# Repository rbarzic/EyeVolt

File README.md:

# Presentation

EyeVolt 2.0 is a **12-channel DC voltage monitor** **and** an **8-channel
programmable DC voltage generator**, both built around a single Raspberry Pi
Pico (the RP2040 `U9`).

On the **monitor** side the Pico continuously samples up to twelve external
voltages and streams the raw ADC readings out over USB-serial, exactly like
v1.1. On the **generation** side the Pico produces eight independent 0 - 3.3 V
outputs by low-pass-filtering eight PWM channels and buffering them; a feedback
multiplexer lets the Pico read its own generated outputs back.

A Python **Terminal User Interface (TUI)** on the PC displays the live
monitored values, progress bars and sparkline trends. The PC software can
optionally expose the readings through an **MCP (Model Context Protocol)
server** so that AI assistants / automation can query the voltages
programmatically.

> **Software status (2.0):** the firmware and PC software currently committed
> in this repository are the **v1.1 code** — they implement the original
> voltage-monitoring protocol only and do **not** yet match the 2.0 hardware.
> See the [Software status](#software-status-20) section below for what works
> today and what is still to be done.

The board has two monitoring domains (unchanged ranges from v1.1):

| Group | Channels | Full-scale | Conditioning | Routed to |
|-------|----------|-----------|--------------|-----------|
| Low-voltage  | 0 - 7  (8 ch) | 0 - 3.3 V | unity-gain buffer only               | MUX0 -> MUX1 (CH4) -> ADC0 (GP26) |
| High-voltage | 8 - 11 (4 ch) | 0 - 6.6 V | buffer + 2:1 resistive divider (÷2)  | MUX1 (CH0-CH3) -> ADC0 (GP26)      |

Because the RP2040 ADC only accepts 0 - 3.3 V, the high-voltage channels are
divided by two on the board (so 6.6 V at the input => 3.3 V at the ADC); the PC
software then multiplies back by two to display the true input voltage.

---

# Hardware

## What changed from v1.1

The 2.0 board keeps the exact same 12-channel voltage-monitoring function and
ranges as v1.1, but the analog multiplexing hardware was reworked, and a full
voltage-generation stage was added:

| Area | v1.1 | v2.0 |
|------|------|------|
| Monitor MUX topology | two independent 74HCT4051, each feeding its own ADC pin (MUX0->GP26, MUX1->GP27) | the two 74HCT4051 are **cascaded** and only **one** ADC pin is used for monitoring (MUX0 -> MUX1 CH4 -> GP26) |
| Monitor select lines | MUX0: S0/S1/S2 = GP10/11/12, MUX1: S0/S1/S2 = GP21/20/19 | MUX0: S0/S1/S2 = **GP12/11/10**, MUX1: S0/S1/S2 = **GP19/20/21** (S0 and S2 swapped on both muxes; `~E` and S1 unchanged) |
| High-voltage input nets | `V55IN0..3` | `V50IN0..3` (same ÷2 divider, same 0 - 6.6 V range — name only) |
| Voltage generation | none | **8 PWM outputs (GP2-GP9)** -> 2nd-order RC low-pass filter -> unity-gain buffer -> J2 output header |
| Output readback | none | a 3rd 74HCT4051 (U12) multiplexes the 8 generated outputs back to **GP27 (ADC1)** |
| Front-panel headers | J2/J3 = TFT/touchscreen (unused) | J2 = **DAC output IDC 2x20** (8 analog outputs + 8 raw PWM taps + power); TFT headers removed |

The input connector **J1** (2x10 box header) is pin-compatible with v1.1.

## Architecture (block-level)

```
                                       Voltage MONITORING                                  Voltage GENERATION
 +-----------+   +-----------------------+                                                    +--------------------+
 |           |V33>+-->|U3/U8 buffer x8 |---VBUFF0..7--> |     | (CH0..7)       PWM GP2..GP9 -->| R(10k)-C(1uF)-R-C  |--> OPA316 buffer x8
 |  J1 input |    |   (0-3.3V domain)  |                 |     |                              |   2nd-order LPF    |     (U4-7,U13-16)
 | connector |    +-----------------------+               |     |                              +--------------------+          |
 | 2x10 box  |            |                              | U11 | (MUX0)                                              0R  | OUT_LINK
 | header    |V50>--+-->|U1 buffer x4|--+  +---+         | 8:1 | ----------+                                           |
 |           |    |   |(high-V in)  |  +->|/2 |->|U2|--> |     |           |   +--------------------+                     |
 |           |    |   +-------------+--+  +---+  (x4)    +-----+           |   | U12 74HCT4051      |                     |
 |           |    |        100k/100k divider               |CH4|----------->| DAC feedback mux   |<--- DAC_OUT0..7 <----+
 |           |    |                                         |     |           | (U12)              |
 +-----------+    |    +-->|U2 buffer x4|---VBUFF8..11--> | U10 | (MUX1)   +--------------------+
                  |    |   |(after div) |                  | 8:1 |                       | common
                  |    |   +------------+                  |     | (CH0..3=HV, CH4=MUX0, | -> GP27 / ADC1 (readback)
                  |    +----------------------------------->|     |  CH5..7=spare)
                                                       +----+-----+
                                                       | common -> GP26 / ADC0 (monitor)
                                                       +----------+
                                                           Raspberry Pi Pico (U9)
        USB-CDC serial  (9600 8N1)  ----> PC running eyevolt_mcp.py
```

In words (monitoring path):

1. The voltages to be measured arrive on connector **J1** (a 2x10 box header).
2. Every input is **buffered** by a rail-to-rail CMOS op-amp configured as a
   unity-gain voltage follower, giving the circuit a very high input impedance
   so it does not perturb the device under test.
   * Low-voltage inputs `V33IN0..3` -> `U3` (MCP6L04 quad); `V33IN4..7` -> `U8`
     (MCP6L04 quad).
   * High-voltage inputs `V50IN0..3` -> `U1` (MCP6L04 quad), then a **100 k /
     100 k divider** (÷2), then buffered again by `U2` (MCP6L04 quad) so the
     divider node is not loaded.
3. The 8 low-voltage buffered signals (`VBUFF0..7`) feed **MUX0** (`U11`, a
   74HCT4051 8:1 analog multiplexer).
4. The 4 high-voltage buffered signals (`VBUFF8..11`) feed channels CH0-CH3 of
   **MUX1** (`U10`, also a 74HCT4051). **MUX0's common output is routed into
   MUX1's CH4 input**, so MUX1 selects between the 4 HV channels and the whole
   MUX0 bank. CH5-CH7 of MUX1 are spare (currently unused).
5. **MUX1's common output goes to ADC0 (GP26)** — this is the only ADC pin used
   for monitoring. The Pico enables MUX1, selects CH4 to reach the MUX0 bank,
   then cycles MUX0 through its 8 channels; for HV channels it selects CH0-CH3
   directly.

Generation path:

1. The Pico generates eight independent PWM signals on **GP2..GP9**
   (`DAC_PWM0..7`).
2. Each PWM signal passes through a **2nd-order passive RC low-pass filter**
   (10 kΩ + 1 µF, then 10 kΩ + 1 µF; per-stage cutoff ≈ 16 Hz) which converts
   the duty cycle into a DC level (0 - 3.3 V proportional to duty cycle).
3. Each filtered DC level is buffered by a unity-gain **OPA316** rail-to-rail
   op-amp (`U4,U5,U6,U7,U13,U14,U15,U16`).
4. A 0 Ω **OUT_LINK** jumper (`R25-R28`, `R45-R48`) ties each buffer output to
   its `DAC_OUTn` net on connector **J2** (the link can be removed to isolate
   or re-route a channel).
5. A third 74HCT4051 (**`U12`**, the *DAC feedback mux*) multiplexes the 8
   `DAC_OUT` signals onto **ADC1 (GP27)** so the firmware can read back every
   generated voltage and verify / trim it.

## Bill of materials (main components)

| Ref | Part | Function |
|-----|------|----------|
| U9 | Raspberry Pi Pico | MCU + dual ADC + USB-serial |
| U11 | 74HCT4051 | 8:1 analog multiplexer for the 3.3 V channels (**MUX0**) |
| U10 | 74HCT4051 | 8:1 analog multiplexer: HV channels CH0-3 + cascaded MUX0 on CH4 + spare CH5-7 (**MUX1**) |
| U12 | 74HCT4051 | 8:1 analog multiplexer for the 8 generated-output readback (**DAC feedback mux**) |
| U3, U8 | MCP6L04 (quad op-amp) | unity-gain buffers for the 8 low-voltage channels |
| U1 | MCP6L04 (quad op-amp) | input buffers for the 4 high-voltage channels |
| U2 | MCP6L04 (quad op-amp) | post-divider buffers for the 4 high-voltage channels |
| U4, U5, U6, U7, U13, U14, U15, U16 | OPA316 (single op-amp, SOT-23-5) | unity-gain buffers for the 8 generated outputs |
| R9-R12 | 100 kΩ | top leg of the 2:1 divider (one per HV channel) |
| R13-R16 | 100 kΩ | bottom leg of the divider to GND (one per HV channel) |
| R1-R8, R17-R24, R29-R44 | 10 kΩ | first and second series resistors of the 8 PWM low-pass filters |
| C3-C18, C27-C42 | 1 µF | filter capacitors of the 8 PWM low-pass filters (each with a DNP thru-hole alternate) |
| R25-R28, R45-R48 | 0 Ω (OUT_LINK) | jumpers linking each output buffer to its `DAC_OUT` net |
| C1-C2, C19-C26, C43-C47 | decoupling | local bypassing for the op-amps and the muxes |
| J1 | Conn_02x10 (2.54 mm box header) | voltage-monitor inputs + GND |
| J2 | IDC 2x20 (2.54 mm) | generation outputs: 8 analog `DAC_OUT`, 8 raw `DAC_PWM` taps, 5 V / 3.3 V / GND |
| H1-H4 | Mounting holes | mechanical |

The monitoring op-amps are Microchip **MCP6L04** (quad, 1 MHz, 85 µA,
rail-to-rail I/O) and the output buffers are TI **OPA316** (single, 2 MHz,
rail-to-rail I/O) — both low-cost, low-bias, supplied from the Pico's 3.3 V
rail. The pin-compatible MCP6024 and OPA4316 are kept as alternatives in
`doc/datasheets/opamp/`.

## Input connector J1 pinout (voltage monitor)

J1 is a 2x10 (2.54 mm) box header. The odd-numbered row carries the eight
low-voltage inputs (`V33IN0..7`); the even-numbered row carries the four
high-voltage inputs (`V50IN0..3`) plus ground. Pinout is compatible with v1.1.

> Pinout below is taken from the generated netlist (`hw/pcb/eyevolt.net`).
> Verify against the current schematic if in doubt.

| J1 pin | Signal   | Range      | EyeVolt channel |
|--------|----------|------------|-----------------|
| 1      | V33IN0   | 0 - 3.3 V  | ch 0  (MUX0 CH0) |
| 3      | V33IN1   | 0 - 3.3 V  | ch 1  (MUX0 CH1) |
| 5      | V33IN2   | 0 - 3.3 V  | ch 2  (MUX0 CH2) |
| 7      | V33IN3   | 0 - 3.3 V  | ch 3  (MUX0 CH3) |
| 9      | V33IN4   | 0 - 3.3 V  | ch 4  (MUX0 CH4) |
| 11     | V33IN5   | 0 - 3.3 V  | ch 5  (MUX0 CH5) |
| 13     | V33IN6   | 0 - 3.3 V  | ch 6  (MUX0 CH6) |
| 15     | V33IN7   | 0 - 3.3 V  | ch 7  (MUX0 CH7) |
| 2      | V50IN0   | 0 - 6.6 V  | ch 8  (MUX1 CH0) |
| 4      | V50IN1   | 0 - 6.6 V  | ch 9  (MUX1 CH1) |
| 6      | V50IN2   | 0 - 6.6 V  | ch 10 (MUX1 CH2) |
| 8      | V50IN3   | 0 - 6.6 V  | ch 11 (MUX1 CH3) |
| 10,12,14,16 | NC  | —          | not connected   |
| 17,18,19,20 | GND | —          | signal / return ground |

## Output connector J2 pinout (voltage generation)

J2 is a 2x20 (2.54 mm) IDC header. Each signal is bussed across a pair of pins
(standard IDC ribbon style). It exposes the 8 **buffered analog outputs**
(`DAC_OUT0..7`), the 8 **raw PWM taps** (`DAC_PWM0..7`, also driven by the
Pico), and the 5 V / 3.3 V / GND power rails.

| J2 pins      | Signal     | Direction | Notes |
|--------------|------------|-----------|-------|
| 1, 2, 3, 4   | GND        | —         | signal / return ground |
| 5, 6         | VDD50      | power out | 5 V (VBUS) rail |
| 7, 8         | VDD33      | power out | 3.3 V rail |
| 9, 10        | DAC_OUT7   | analog out| buffered generated output 7 |
| 11, 12       | DAC_OUT6   | analog out| buffered generated output 6 |
| 13, 14       | DAC_OUT5   | analog out| buffered generated output 5 |
| 15, 16       | DAC_OUT4   | analog out| buffered generated output 4 |
| 17, 18       | DAC_OUT3   | analog out| buffered generated output 3 |
| 19, 20       | DAC_OUT2   | analog out| buffered generated output 2 |
| 21, 22       | DAC_OUT1   | analog out| buffered generated output 1 |
| 23, 24       | DAC_OUT0   | analog out| buffered generated output 0 |
| 25, 26       | DAC_PWM7   | digital   | raw PWM tap 7 (driven by GP9) |
| 27, 28       | DAC_PWM6   | digital   | raw PWM tap 6 (driven by GP8) |
| 29, 30       | DAC_PWM5   | digital   | raw PWM tap 5 (driven by GP7) |
| 31, 32       | DAC_PWM4   | digital   | raw PWM tap 4 (driven by GP6) |
| 33, 34       | DAC_PWM3   | digital   | raw PWM tap 3 (driven by GP5) |
| 35, 36       | DAC_PWM2   | digital   | raw PWM tap 2 (driven by GP4) |
| 37, 38       | DAC_PWM1   | digital   | raw PWM tap 1 (driven by GP3) |
| 39, 40       | DAC_PWM0   | digital   | raw PWM tap 0 (driven by GP2) |

## Analog conditioning detail

* **Low-voltage channels (0-7):** each input drives the `+` input of an op-amp
  voltage follower whose output is shorted to its `-` input. The output
  (`VBUFF0..7`) goes directly to one of MUX0's analog inputs. No scaling — the
  displayed voltage equals the measured voltage (up to the 3.3 V rail).

* **High-voltage channels (8-11):** each input is first buffered (U1, high
  impedance), then split by a 100 k / 100 k divider to GND, then buffered again
  (U2) before reaching MUX1. The two-stage buffering keeps the divider node
  high-impedance and accurate. The ADC therefore sees `Vin / 2`, and the PC
  software restores the real value by multiplying by 2 (`raw / 65536 * 6.6`).

## Multiplexing (74HCT4051)

Each 74HCT4051 selects one of 8 analog inputs onto a common pin `A` according to
the 3-bit address `S2 S1 S0`, while `~E` (active-low enable) gates the output.
When `~E = 1` the switch is high-impedance. The Pico drives these logic pins
directly. On the board, VEE is tied to GND (single-supply operation, 0 - VCC
analog range) and VCC is the 3.3 V rail.

**Monitor cascade:** in 2.0, MUX0's common is wired to **MUX1 channel 4**, so
the firmware must (a) enable MUX1 and address CH4 to "see through" to the
8 low-voltage channels, then (b) cycle MUX0; the high-voltage channels are read
by addressing MUX1 CH0-CH3 directly. All twelve channels exit on **GP26**.

**Feedback mux:** `U12` independently switches the 8 generated `DAC_OUT`
signals onto **GP27** so each output voltage can be measured back by the Pico.

## PWM generation chain

Each of the 8 output channels is identical:

```
GPn (PWM) -- R 10k -- (C 1uF to GND) -- R 10k -- (C 1uF to GND) -- OPA316 unity buffer -- 0R OUT_LINK -- DAC_OUTn -> J2
```

This is a 2nd-order passive RC low-pass filter (per-stage cutoff
`1/(2*pi*10k*1uF) ≈ 16 Hz`) followed by a rail-to-rail unity-gain buffer. The
steady-state output is `duty * 3.3 V` over the 0 - 3.3 V range. The filter
strongly attenuates the PWM carrier so the output is essentially DC; the buffer
provides a low-impedance output to the load via J2.

## Power

The board is powered by the Pico's USB connection. The 3.3 V rail (`VDD33`)
powers the op-amps and the multiplexers and serves as the ADC reference. A 5 V
rail (`VDD50` = VBUS) is also present and is exposed on the J2 output header.

---

# Firmware (Pico, MicroPython)

Location: `sw/pico/micropython/main.py`. It is plain MicroPython using the
`machine` module; `boot.py` is empty (USB-CDC is configured in the firmware
image, not at run time).

## Pico pin mapping (2.0 hardware)

| GPIO | Direction | Net (schematic) | Purpose |
|------|-----------|-----------------|---------|
| GP2  | out (PWM) | DAC_PWM0 | generation PWM, output 0 |
| GP3  | out (PWM) | DAC_PWM1 | generation PWM, output 1 |
| GP4  | out (PWM) | DAC_PWM2 | generation PWM, output 2 |
| GP5  | out (PWM) | DAC_PWM3 | generation PWM, output 3 |
| GP6  | out (PWM) | DAC_PWM4 | generation PWM, output 4 |
| GP7  | out (PWM) | DAC_PWM5 | generation PWM, output 5 |
| GP8  | out (PWM) | DAC_PWM6 | generation PWM, output 6 |
| GP9  | out (PWM) | DAC_PWM7 | generation PWM, output 7 |
| GP10 | out | MUX0_S2 | MUX0 address bit 2 |
| GP11 | out | MUX0_S1 | MUX0 address bit 1 |
| GP12 | out | MUX0_S0 | MUX0 address bit 0 |
| GP13 | out | MUX0_EB | MUX0 enable (`~E`, active low) |
| GP14 | out | DACMUX_S1 | DAC feedback mux address bit 1 |
| GP15 | out | DACMUX_S0 | DAC feedback mux address bit 0 |
| GP16 | out | DACMUX_S2 | DAC feedback mux address bit 2 |
| GP17 | out | DACMUX_EB | DAC feedback mux enable (`~E`, active low) |
| GP18 | out | MUX1_EB | MUX1 enable (`~E`, active low) |
| GP19 | out | MUX1_S0 | MUX1 address bit 0 |
| GP20 | out | MUX1_S1 | MUX1 address bit 1 |
| GP21 | out | MUX1_S2 | MUX1 address bit 2 |
| GP26 | in (ADC0) | MON_ADC_A | MUX1 common -> reads all 12 monitor channels (LV via cascade) |
| GP27 | in (ADC1) | DAC_FB_A | DAC feedback mux common -> reads back the 8 generated outputs |

## Principle of operation (v1.1-compatible monitoring)

> The firmware currently checked in (`main.py`) is the **v1.1** firmware: it
> drives MUX0 / MUX1 as two independent muxes and reads **two** ADC pins
> (GP26 + GP27). On the **2.0** hardware this is incorrect — MUX1's select
> lines are remapped and all 12 channels now arrive on **GP26 only** (GP27 is
> the DAC-feedback ADC). See [Software status](#software-status-20).

The intended v1.1-compatible scan (to be re-implemented for 2.0) repeatedly:

1. Selects **MUX1 CH4** (the cascade), then scans **MUX0** channels 0..7: for
   each channel it writes the 3-bit MUX0 address, asserts `~E`, waits for the
   switch and buffer to settle, then reads **ADC0 (GP26)**.
2. Scans **MUX1** channels 0..3 (the HV channels) directly, reading ADC0.
3. Prints two text lines (one per group) over USB-serial.

`read_u16()` returns a 16-bit value (0..65535) proportional to the voltage at
the ADC pin relative to the 3.3 V reference. The firmware sends the *raw* value
unchanged; all scaling is done on the PC side.

## Serial protocol

USB-CDC, **9600 baud, 8N1**, ASCII text. The Pico emits two lines per cycle:

```
1::VVVVV VVVVV VVVVV VVVVV VVVVV VVVVV VVVVV VVVVV
2::VVVVV VVVVV VVVVV VVVVV
```

* `1::` introduces the 8 low-voltage channels (0..7), space-separated,
  zero-padded to 5 digits.
* `2::` introduces the 4 high-voltage channels (8..11), space-separated.
* Values are raw 16-bit ADC codes (0..65535).

There is no request/response framing and no checksum: the device streams
continuously and the host synchronises on the `1::` / `2::` headers. The 2.0
firmware will keep this protocol so the PC software and the MCP tools remain
backward-compatible.

---

# PC software

The recommended version is `sw/pc/eyevolt_mcp.py` (a richer superset of the
older `sw/pc/eyevolt_pc.py`). It is a single-file Python application built with
**Textual** (TUI), **pyserial-asyncio** (serial), and an optional **MCP over
SSE** server (Starlette + Uvicorn).

## Serial acquisition & scaling

`SerialProtocol` buffers bytes until a newline, then `process_line()` decodes
each frame:

* `1::` frame -> 8 integers, converted with `raw / 65536 * 3.3`  (volts, 0-3.3 V)
* `2::` frame -> 4 integers, converted with `raw / 65536 * 6.6`  (volts, 0-6.6 V)

The resulting 12 float values are pushed into the 12 display widgets.

## Terminal User Interface (TUI)

`SerialTUI` lays out **12 `VoltageDisplay` widgets in a 3x4 grid**. Each widget
contains a label with the channel name and current value, a progress bar
showing the value as a percentage of the channel full-scale (3.3 V for
channels 0-7, 6.6 V for channels 8-11), and a sparkline of recent history
(rolling window, default 128 samples). A colour scheme highlights abnormal
rails:

| Voltage | Colour |
|---------|--------|
| < 0.5 V     | white  |
| 0.5 - 0.8 V | yellow |
| 0.8 - 1.2 V | green  |
| >= 1.2 V    | red    |

## MCP server

When started with `--mcp`, an `EyeVoltMCPServer` runs an MCP server over
Server-Sent Events (SSE) on `127.0.0.1:8088` by default, in a background
thread. It exposes the live readings as tools that an MCP-compatible client
(e.g. an AI coding assistant) can call:

| Tool | Description |
|------|-------------|
| `get_voltages`        | All enabled channels as `{name: voltage}` |
| `get_voltage`         | One channel by name |
| `get_voltage_idx`     | One channel by index (0-11) |
| `get_channel_info`    | Full per-channel info (name, enabled, voltage, max) |
| `get_channel_history` | Sparkline history (percentages 0-100) for a named channel |

## Command-line usage

```
eyevolt_mcp.py [-h] [--text VAL=NAME,...] [--channel VAL=on|off,...]
               [--history N] [--mcp] [--mcp-host H] [--mcp-port P] [-v]
               PORT
```

* `PORT` — serial device, e.g. `/dev/ttyACM0` (Linux/macOS) or `COM3` (Windows).
* `--text` — rename channels, zero-based, e.g. `val0=VCORE,val1=VIO`.
* `--channel` — enable/disable channels, e.g. `val8=off,val9=off`. Channels not
  listed default to **on**; disabled channels show `----`.
* `--history` — sparkline length (default 128).
* `--mcp` — start the MCP/SSE server.
* `--mcp-host` / `--mcp-port` — MCP bind address (default `127.0.0.1:8088`).
* `-v` / `-vv` — info / debug logging.

Examples (see `sw/pc/readme.txt`):

```
./eyevolt_mcp.py --text val0=VCORE,val1=VIO /dev/ttyACM0

./eyevolt_mcp.py \
    --text val0=VCORE,val1=VMAX,val2=VMAIN,val3=VULP,val4=VPERIPH,\
val5=VCOREDIG,val6=VCORERAD,val7=VIO \
    --channel val8=off,val9=off,val10=off,val11=off \
    /dev/ttyACM0

./eyevolt_mcp.py --mcp /dev/ttyACM0        # also expose readings to MCP clients
```

---

# Software status (2.0)

The hardware described above is the **2.0** design, but the software in this
repository is still the **v1.1** implementation. Concretely:

| Feature | Status |
|---------|--------|
| 12-channel voltage monitoring (serial protocol `1::`/`2::`) | **Planned.** The protocol and PC side stay the same; only the Pico scan routine changes for the 2.0 MUX cascade / remapped select lines. The intent is for the device to expose the **same** v1.1 monitoring protocol by default. |
| Current `main.py` on 2.0 hardware | **Does not work as-is.** It uses two ADC pins and the v1.1 select-line mapping; on 2.0 all 12 channels arrive on GP26 and GP27 is the DAC-feedback ADC. |
| 8-channel voltage generation (PWM + filter + buffer) | **Not implemented.** Requires new firmware (PWM setup on GP2-GP9, duty-cycle commands) and PC/MCP tooling to set voltages. |
| Output readback via U12 / GP27 | **Not implemented.** Needs firmware + PC support to read and report generated voltages. |
| PC TUI / MCP server | **Working**, unchanged from v1.1 (monitoring only). |

### What the 2.0 firmware update needs (monitoring)

* Drive MUX0 select lines on the **new** GPIOs (S0=GP12, S1=GP11, S2=GP10).
* Drive MUX1 select lines on the **new** GPIOs (S0=GP19, S1=GP20, S2=GP21).
* To read the 8 low-voltage channels: enable MUX1, select **CH4** (cascade),
  then cycle MUX0 0..7 and read **ADC0 (GP26)**.
* To read the 4 high-voltage channels: select MUX1 **CH0..CH3** and read ADC0.
* Keep emitting the `1::` (8 values) / `2::` (4 values) lines so the PC
  software and MCP tools are unchanged.

### What the 2.0 generation feature needs

* PWM setup on GP2-GP9 with a carrier frequency well above the 16 Hz filter
  cutoff.
* A serial command set to set per-channel duty cycle (target voltage).
* Readback of the 8 `DAC_OUT` signals through U12 on **GP27 (ADC1)**.
* PC / MCP tooling to set and monitor the 8 generated voltages.

---

# Running the system end-to-end

1. **Flash the Pico** with a MicroPython image (USB-CDC enabled), then copy
   `sw/pico/micropython/main.py` onto it (the `sw/pico/micropython/Makefile`
   provides `make copy` via `rshell` and `make run` via `mpremote`). On power-up
   the Pico starts streaming `1::`/`2::` lines at 9600 baud.
2. **Set up the PC environment** (`requirements.txt`):
   `pip install -r requirements.txt` (textual, pyserial-asyncio, mcp, starlette,
   uvicorn, rich, ...).
3. **Run the TUI**, pointing it at the Pico's serial port and labelling the
   channels to match your DUT (example above).
4. **(Optional)** add `--mcp` and connect an MCP client to `http://127.0.0.1:8088/sse`.

> Note: step 1 assumes the firmware already matches the 2.0 monitoring routing.
> Until that update is done, the device will not produce correct readings on
> 2.0 hardware (see [Software status](#software-status-20)).

---

# End-to-end data path (summary)

```
MONITORING:
DUT rail -- J1 -- op-amp buffer (+÷2 divider on HV channels)
        -- 74HCT4051 MUX0 -> MUX1 CH4 / MUX1 CH0..3 (U11 -> U10, selected by GP10..13, GP19..21, GP18)
        -- Pico ADC0 (GP26)
        -- MicroPython reads raw 16-bit codes, prints "1::.." / "2::.."
        -- USB-CDC @9600 baud
        -- eyevolt_mcp.py (async serial reader)
        -- Textual TUI (value + bar + sparkline) and/or MCP/SSE server

GENERATION (not yet implemented):
PC target voltage -> serial command -> Pico sets PWM duty on GP2..GP9
        -> 2nd-order RC LPF (10k/1uF, ~16 Hz) -> OPA316 unity buffer
        -> 0R OUT_LINK -> DAC_OUT0..7 -> J2
        -> (readback) U12 74HCT4051 feedback mux -> Pico ADC1 (GP27)
```

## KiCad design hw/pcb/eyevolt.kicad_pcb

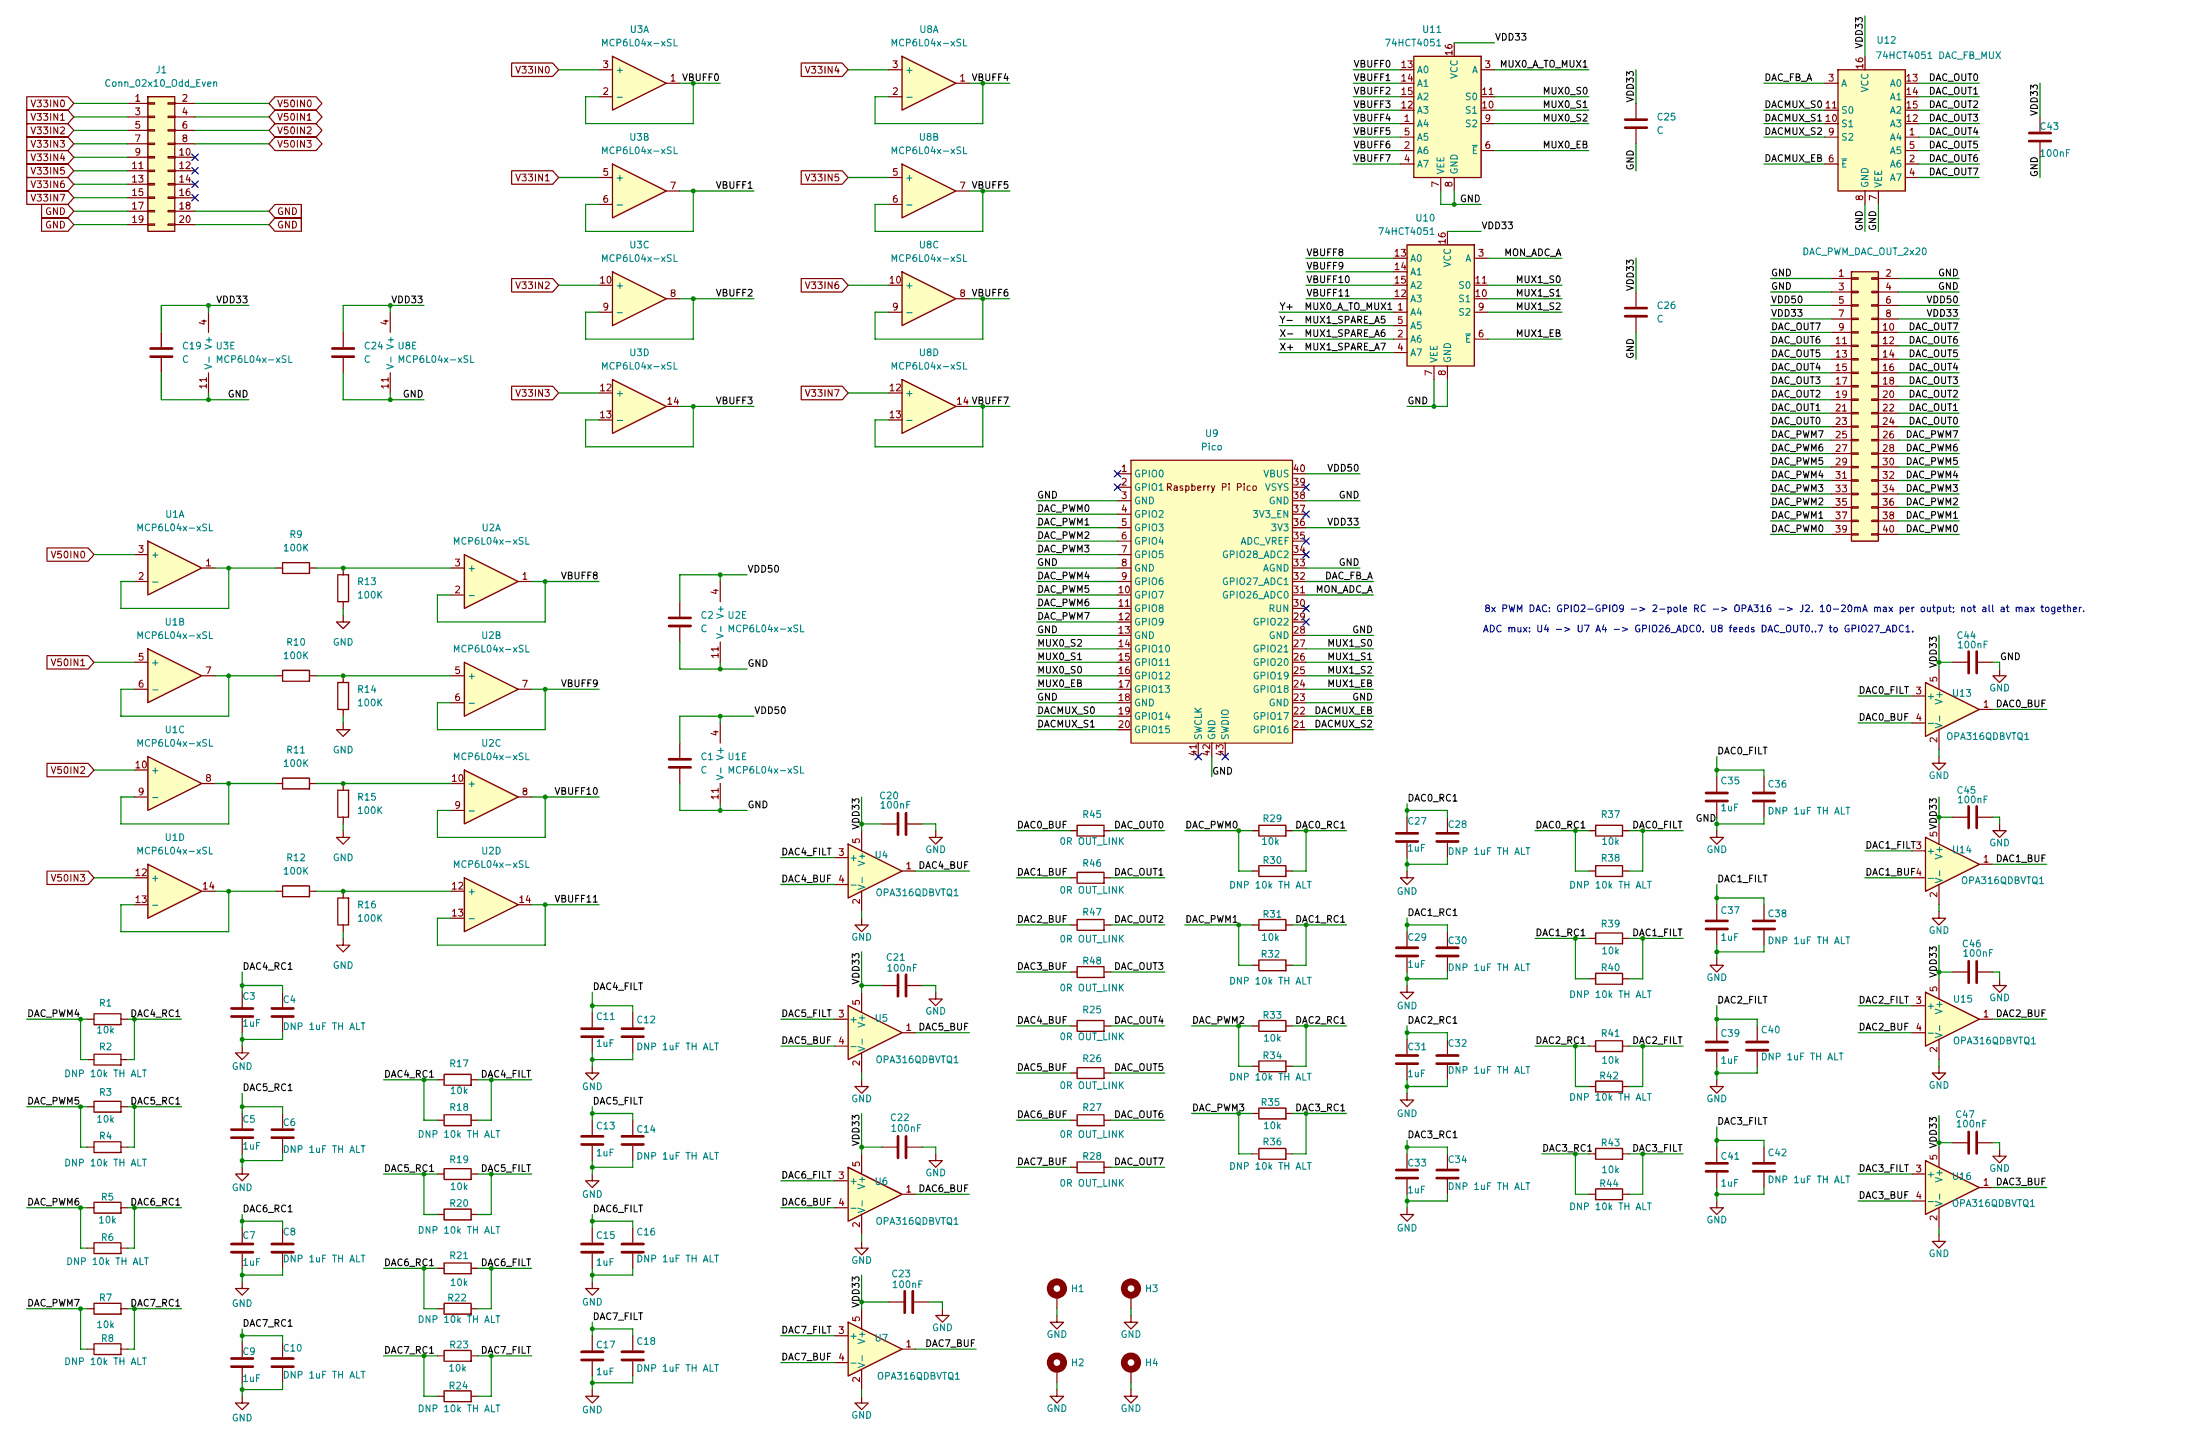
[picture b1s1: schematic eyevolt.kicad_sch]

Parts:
C1, C2, C19, C24, C25, C26: C; C_0805_2012Metric_Pad1.18x1.45mm_HandSolder
C3, C5, C7, C9, C11, C13, C15, C17, C27, C29, C31, C33, C35, C37, C39, C41: 1uF; C_0805_2012Metric_Pad1.18x1.45mm_HandSolder
C4, C6, C8, C10, C12, C14, C16, C18, C28, C30, C32, C34, C36, C38, C40, C42: DNP 1uF TH ALT; C_Disc_D5.0mm_W2.5mm_P5.00mm
C20, C21, C22, C23, C43, C44, C45, C46, C47: 100nF; C_0805_2012Metric
H1, H2, H3, H4: MountingHole_Pad; MountingHole_3.5mm_Pad_Via
J1: Conn_02x10_Odd_Even; PinHeader_2x10_P2.54mm_Horizontal
J2: DAC_PWM_DAC_OUT_2x20; IDC-Header_2x20_P2.54mm_Horizontal
R1, R3, R5, R7, R17, R19, R21, R23, R29, R31, R33, R35, R37, R39, R41, R43: 10k; R_0805_2012Metric_Pad1.20x1.40mm_HandSolder
R2, R4, R6, R8, R18, R20, R22, R24, R30, R32, R34, R36, R38, R40, R42, R44: DNP 10k TH ALT; R_Axial_DIN0207_L6.3mm_D2.5mm_P7.62mm_Horizontal
R9, R10, R11, R12, R13, R14, R15, R16: 100K; R_0805_2012Metric_Pad1.20x1.40mm_HandSolder
R25, R26, R27, R28, R45, R46, R47, R48: 0R OUT_LINK; R_0805_2012Metric_Pad1.20x1.40mm_HandSolder
U1, U2, U3, U8: MCP6L04x-xSL; SOIC-14_3.9x8.7mm_P1.27mm
U4, U5, U6, U7, U13, U14, U15, U16: OPA316QDBVTQ1; SOT-23-5
U9: Pico; RPi_Pico_SMD_TH
U10, U11: 74HCT4051; SOIC-16_3.9x9.9mm_P1.27mm
U12: 74HCT4051 DAC_FB_MUX; SOIC-16_3.9x9.9mm_P1.27mm

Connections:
/DAC0_BUF: R45.1, U13.1, U13.4 (-)
/DAC0_FILT: C35.1, C36.1, R37.2, R38.2, U13.3 (+)
/DAC0_RC1: C27.1, C28.1, R29.2, R30.2, R37.1, R38.1
/DAC1_BUF: R46.1, U14.1, U14.4 (-)
/DAC1_FILT: C37.1, C38.1, R39.2, R40.2, U14.3 (+)
/DAC1_RC1: C29.1, C30.1, R31.2, R32.2, R39.1, R40.1
/DAC2_BUF: R47.1, U15.1, U15.4 (-)
/DAC2_FILT: C39.1, C40.1, R41.2, R42.2, U15.3 (+)
/DAC2_RC1: C31.1, C32.1, R33.2, R34.2, R41.1, R42.1
/DAC3_BUF: R48.1, U16.1, U16.4 (-)
/DAC3_FILT: C41.1, C42.1, R43.2, R44.2, U16.3 (+)
/DAC3_RC1: C33.1, C34.1, R35.2, R36.2, R43.1, R44.1
/DAC4_BUF: R25.1, U4.1, U4.4 (-)
/DAC4_FILT: C11.1, C12.1, R17.2, R18.2, U4.3 (+)
/DAC4_RC1: C3.1, C4.1, R1.2, R2.2, R17.1, R18.1
/DAC5_BUF: R26.1, U5.1, U5.4 (-)
/DAC5_FILT: C13.1, C14.1, R19.2, R20.2, U5.3 (+)
/DAC5_RC1: C5.1, C6.1, R3.2, R4.2, R19.1, R20.1
/DAC6_BUF: R27.1, U6.1, U6.4 (-)
/DAC6_FILT: C15.1, C16.1, R21.2, R22.2, U6.3 (+)
/DAC6_RC1: C7.1, C8.1, R5.2, R6.2, R21.1, R22.1
/DAC7_BUF: R28.1, U7.1, U7.4 (-)
/DAC7_FILT: C17.1, C18.1, R23.2, R24.2, U7.3 (+)
/DAC7_RC1: C9.1, C10.1, R7.2, R8.2, R23.1, R24.1
/DACMUX_EB: U9.22 (GPIO17), U12.6 (~E)
/DACMUX_S2: U9.21 (GPIO16), U12.9 (S2)
/DAC_FB_A: U9.32 (GPIO27_ADC1), U12.3 (A)
/DAC_OUT0: J2.23, J2.24, R45.2, U12.13 (A0)
/DAC_OUT1: J2.21, J2.22, R46.2, U12.14 (A1)
/DAC_OUT2: J2.19, J2.20, R47.2, U12.15 (A2)
/DAC_OUT3: J2.17, J2.18, R48.2, U12.12 (A3)
/DAC_OUT4: J2.15, J2.16, R25.2, U12.1 (A4)
/DAC_OUT5: J2.13, J2.14, R26.2, U12.5 (A5)
/DAC_OUT6: J2.11, J2.12, R27.2, U12.2 (A6)
/DAC_OUT7: J2.9, J2.10, R28.2, U12.4 (A7)
/DAC_PWM0: J2.39, J2.40, R29.1, R30.1, U9.4 (GPIO2)
/DAC_PWM1: J2.37, J2.38, R31.1, R32.1, U9.5 (GPIO3)
/DAC_PWM2: J2.35, J2.36, R33.1, R34.1, U9.6 (GPIO4)
/DAC_PWM3: J2.33, J2.34, R35.1, R36.1, U9.7 (GPIO5)
/DAC_PWM4: J2.31, J2.32, R1.1, R2.1, U9.9 (GPIO6)
/DAC_PWM5: J2.29, J2.30, R3.1, R4.1, U9.10 (GPIO7)
/DAC_PWM6: J2.27, J2.28, R5.1, R6.1, U9.11 (GPIO8)
/DAC_PWM7: J2.25, J2.26, R7.1, R8.1, U9.12 (GPIO9)
/MON_ADC_A: U9.31 (GPIO26_ADC0), U10.3 (A)
/MUX0_A_TO_MUX1: U10.1 (A4), U11.3 (A)
/MUX0_EB: U9.17 (GPIO13), U11.6 (~E)
/MUX0_S0: U9.16 (GPIO12), U11.11 (S0)
/MUX0_S1: U9.15 (GPIO11), U11.10 (S1)
/MUX0_S2: U9.14 (GPIO10), U11.9 (S2)
/MUX1_EB: U9.24 (GPIO18), U10.6 (~E)
/MUX1_S1: U9.26 (GPIO20), U10.10 (S1)
/MUX1_SPARE_A5: U10.5 (A5)
/MUX1_SPARE_A6: U10.2 (A6)
/MUX1_SPARE_A7: U10.4 (A7)
/VBUFF0: U3.1, U3.2 (-), U11.13 (A0)
/VBUFF1: U3.6 (-), U3.7, U11.14 (A1)
/VBUFF2: U3.8, U3.9 (-), U11.15 (A2)
/VBUFF3: U3.13 (-), U3.14, U11.12 (A3)
/VBUFF4: U8.1, U8.2 (-), U11.1 (A4)
/VBUFF5: U8.6 (-), U8.7, U11.5 (A5)
/VBUFF6: U8.8, U8.9 (-), U11.2 (A6)
/VBUFF7: U8.13 (-), U8.14, U11.4 (A7)
/VBUFF8: U2.1, U2.2 (-), U10.13 (A0)
/VBUFF9: U2.6 (-), U2.7, U10.14 (A1)
/VBUFF10: U2.8, U2.9 (-), U10.15 (A2)
/VBUFF11: U2.13 (-), U2.14, U10.12 (A3)
/VDD33: C19.1, C20.1, C21.1, C22.1, C23.1, C24.1, C25.1, C26.1, C43.1, C44.1, C45.1, C46.1, C47.1, J2.7, J2.8, U3.4 (V+), U4.5 (V+), U5.5 (V+), U6.5 (V+), U7.5 (V+), U8.4 (V+), U9.36 (3V3), U10.16 (VCC), U11.16 (VCC), U12.16 (VCC), U13.5 (V+), U14.5 (V+), U15.5 (V+), U16.5 (V+)
/VDD50: C1.1, C2.1, J2.5, J2.6, U1.4 (V+), U2.4 (V+), U9.40 (VBUS)
GND: C1.2, C2.2, C3.2, C4.2, C5.2, C6.2, C7.2, C8.2, C9.2, C10.2, C11.2, C12.2, C13.2, C14.2, C15.2, C16.2, C17.2, C18.2, C19.2, C20.2, C21.2, C22.2, C23.2, C24.2, C25.2, C26.2, C27.2, C28.2, C29.2, C30.2, C31.2, C32.2, C33.2, C34.2, C35.2, C36.2, C37.2, C38.2, C39.2, C40.2, C41.2, C42.2, C43.2, C44.2, C45.2, C46.2, C47.2, H1.1 (1_1), H2.1 (1_1), H3.1 (1_1), H4.1 (1_1), J1.17, J1.18, J1.19, J1.20, J2.1, J2.2, J2.3, J2.4, R13.1, R14.1, R15.1, R16.1, U1.11 (V-), U2.11 (V-), U3.11 (V-), U4.2 (V-), U5.2 (V-), U6.2 (V-), U7.2 (V-), U8.11 (V-), U9.3 (GND), U9.8 (GND), U9.13 (GND), U9.18 (GND), U9.23 (GND), U9.28 (GND), U9.33 (AGND), U9.38 (GND), U9.42 (GND), U10.7 (VEE), U10.8 (GND), U11.7 (VEE), U11.8 (GND), U12.7 (VEE), U12.8 (GND), U13.2 (V-), U14.2 (V-), U15.2 (V-), U16.2 (V-)
unnamed: R9.1, U1.1, U1.2 (-)
unnamed: R10.1, U1.6 (-), U1.7
unnamed: R11.1, U1.8, U1.9 (-)
unnamed: R12.1, U1.13 (-), U1.14
unnamed: R9.2, R13.2, U2.3 (+)
unnamed: R10.2, R14.2, U2.5 (+)
unnamed: R11.2, R15.2, U2.10 (+)
unnamed: R12.2, R16.2, U2.12 (+)
V33IN0: J1.1, U3.3 (+)
V33IN1: J1.3, U3.5 (+)
V33IN2: J1.5, U3.10 (+)
V33IN3: J1.7, U3.12 (+)
V33IN4: J1.9, U8.3 (+)
V33IN5: J1.11, U8.5 (+)
V33IN6: J1.13, U8.10 (+)
V33IN7: J1.15, U8.12 (+)
V50IN0: J1.2, U1.3 (+)
V50IN1: J1.4, U1.5 (+)
V50IN2: J1.6, U1.10 (+)
V50IN3: J1.8, U1.12 (+)

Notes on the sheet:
8x PWM DAC: GPIO2-GPIO9 -> 2-pole RC -> OPA316 -> J2. 10-20mA max per output; not all at max together.
ADC mux: U4 -> U7 A4 -> GPIO26_ADC0. U8 feeds DAC_OUT0..7 to GPIO27_ADC1.

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
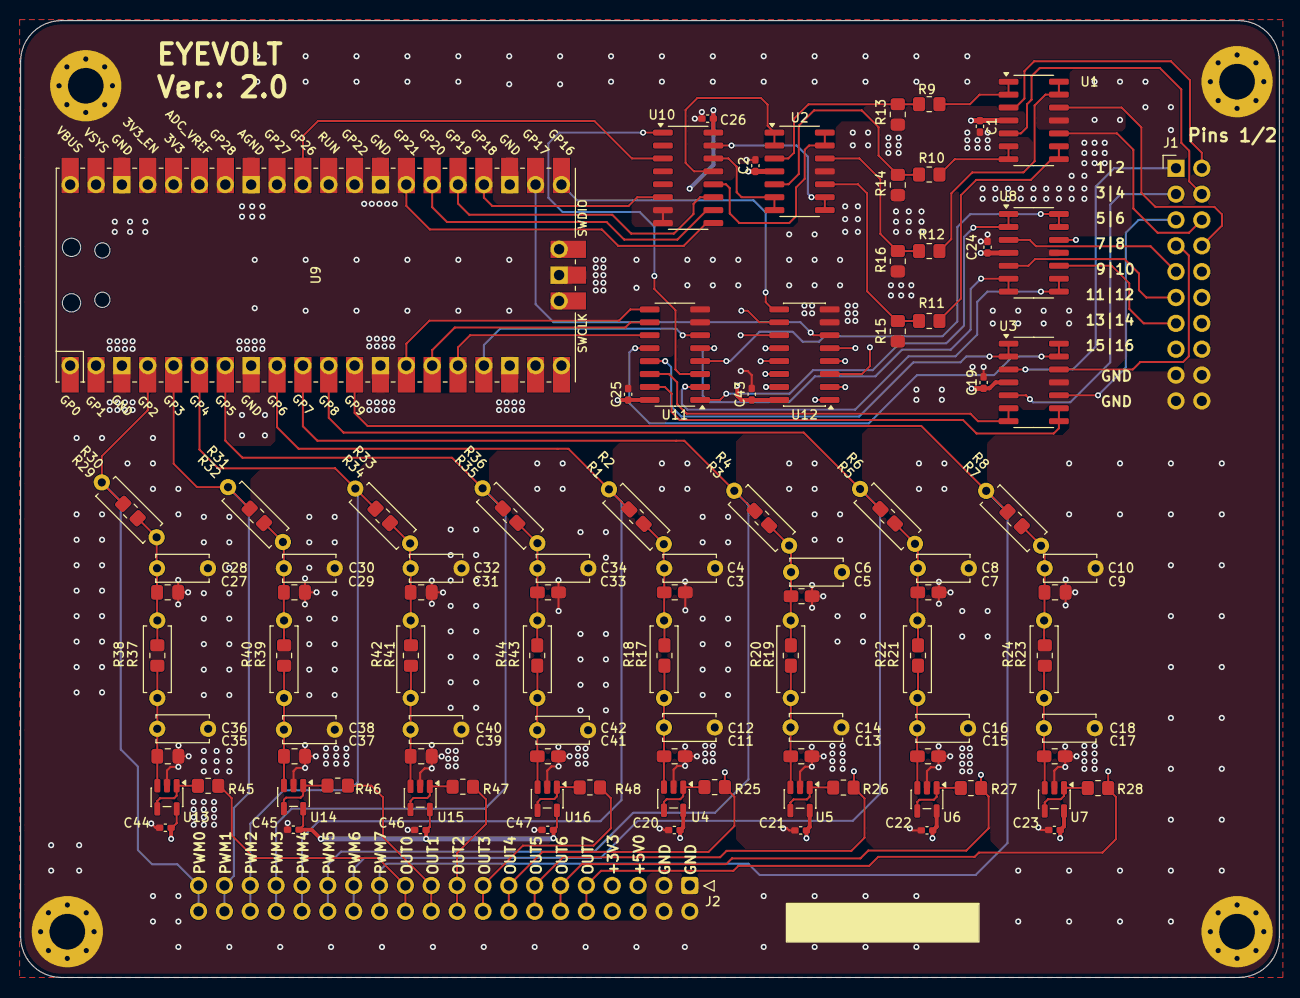
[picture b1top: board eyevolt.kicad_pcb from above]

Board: 4 copper layers, 123.7 x 94.0 mm, 117 parts (0 on the bottom side), 90 nets.

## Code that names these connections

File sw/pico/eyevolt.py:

from machine import Pin,ADC
from time import sleep

led = Pin('LED', Pin.OUT)
print('Blinking LED Example')

adc0 = ADC(26)
adc1 = ADC(27)

mux0_eb = Pin('GPIO13', Pin.OUT)
mux0_S0 = Pin('GPIO10', Pin.OUT)
mux0_S1 = Pin('GPIO11', Pin.OUT)
mux0_S2 = Pin('GPIO12', Pin.OUT)

mux1_eb = Pin('GPIO18', Pin.OUT)
mux1_S0 = Pin('GPIO21', Pin.OUT)
mux1_S1 = Pin('GPIO20', Pin.OUT)
mux1_S2 = Pin('GPIO19', Pin.OUT)


def mux0 (channel):
  b0 = channel & 1
  b1 = (channel & 2)>>1
  b2 = (channel & 4)>>2
  
  mux0_S0.value(b0) 
  mux0_S1.value(b1)
  mux0_S2.value(b2)
  mux0_eb.value(0)

def mux1 (channel):
  b0 = channel & 1
  b1 = (channel & 2)>>1
  b2 = (channel & 4)>>2
  
  mux1_S0.value(b0) 
  mux1_S1.value(b1)
  mux1_S2.value(b2)
  mux1_eb.value(0)

mux0(4)
mux1(0) 

while True:
  led.value(not led.value())
  adc_data0 = adc0.read_u16()
  adc_data1 = adc1.read_u16()
  print(f"ADC0 {(adc_data0 / 65535)*3.3}")
  print(f"ADC1 {(adc_data1 / 65535)*3.3*0.5}")
  
  sleep(0.5)

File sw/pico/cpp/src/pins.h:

#pragma once

//
// EyeVolt 2.0 — Pico (RP2040) hardware pin map.
//
// Source of truth for the v2.0 PCB. See the project README.md section
// "Pico pin mapping (2.0 hardware)". Key differences from v1.1:
//   * MUX0 and MUX1 are CASCADED; all 12 monitor channels exit on GP26 only.
//   * S0 and S2 are swapped on both monitor muxes vs v1.1.
//   * GP27 is now the DAC-feedback ADC (was MUX1 monitor ADC in v1.1).
//   * GP2-GP9 drive the 8 PWM generation outputs (new in v2.0).
//

namespace pins {

// ── Monitor mux MUX0 (U11): 8 low-voltage channels ──────────────────────────
// (S0/S2 swapped vs v1.1: v1.1 had S0=GP10, S2=GP12)
constexpr unsigned MUX0_S0 = 12;
constexpr unsigned MUX0_S1 = 11;
constexpr unsigned MUX0_S2 = 10;
constexpr unsigned MUX0_EN = 13;   // ~E, active low

// ── Monitor mux MUX1 (U10): HV channels CH0-3, cascade MUX0 on CH4 ───────────
// (S0/S2 swapped vs v1.1: v1.1 had S0=GP21, S2=GP19)
constexpr unsigned MUX1_S0 = 19;
constexpr unsigned MUX1_S1 = 20;
constexpr unsigned MUX1_S2 = 21;
constexpr unsigned MUX1_EN = 18;   // ~E, active low

// MUX1 channel that taps the cascaded MUX0 bank (low-voltage inputs).
constexpr unsigned MUX1_CASCADE_CHANNEL = 4;

// ── DAC feedback mux U12: reads back 8 generated outputs ─────────────────────
constexpr unsigned DACMUX_S0 = 15;
constexpr unsigned DACMUX_S1 = 14;
constexpr unsigned DACMUX_S2 = 16;
constexpr unsigned DACMUX_EN = 17;   // ~E, active low

// ── ADC inputs ───────────────────────────────────────────────────────────────
// RP2040 ADC input number (not the GPIO number): input 0 = GP26, input 1 = GP27.
constexpr unsigned ADC_MONITOR  = 0;   // GP26 — all 12 monitor channels (via MUX1)
constexpr unsigned ADC_READBACK = 1;   // GP27 — 8 generated-output readback (via U12)

constexpr unsigned ADC_MONITOR_PIN  = 26;
constexpr unsigned ADC_READBACK_PIN = 27;

// ── PWM generation outputs (GP2-GP9 → DAC_PWM0..7) ───────────────────────────
constexpr unsigned DAC_PWM_FIRST = 2;    // DAC_PWM0 = GP2
constexpr unsigned NUM_DAC_CHANNELS = 8;

// ── Channel counts ───────────────────────────────────────────────────────────
constexpr unsigned NUM_LV_CHANNELS      = 8;   // channels 0-7  (0 - 3.3 V)
constexpr unsigned NUM_HV_CHANNELS      = 4;   // channels 8-11 (0 - 6.6 V)
constexpr unsigned NUM_MONITOR_CHANNELS = 12;

// ── Timing ───────────────────────────────────────────────────────────────────
// Settle time after switching a mux before sampling the ADC.
// The buffers (MCP6L04 / OPA316) and the 74HCT4051 settle in well under 1 us;
// 1 ms is a very safe margin and yields a fast (~50 Hz) refresh.
constexpr unsigned MUX_SETTLE_US      = 1000;
constexpr unsigned READBACK_SETTLE_US = 1000;

// ADC samples averaged per reading to suppress RP2040 ADC noise.
constexpr unsigned ADC_OVERSAMPLE = 4;

// Full-scale of the generation outputs (3.3 V rail), in millivolts.
constexpr unsigned DAC_FULLSCALE_MV = 3300;
constexpr unsigned DAC_MAX_RAW      = 65535;

// ── Waveform playback ────────────────────────────────────────────────────────
// Max steps in a loaded waveform. Buffer size = WF_MAX_STEPS * 8 ch * 2 B.
constexpr unsigned WF_MAX_STEPS         = 2048;   // 32 KB @ 8 channels
constexpr unsigned WF_DEFAULT_STEP_US   = 1000;   // 1 ms/step → 2.048 s full run
constexpr unsigned WF_MIN_STEP_US       = 200;    // 5000 steps/s upper bound
constexpr unsigned WF_MAX_STEP_US       = 100000; // 10 steps/s lower bound
constexpr unsigned WF_UPLOAD_TIMEOUT_MS = 5000;   // abort a stalled binary upload

}  // namespace pins

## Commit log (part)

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2024-02-08 Add first directories
2024-02-08 Add more directories
2024-02-08 Add documentation for RPi Pico, + analog mux
2024-02-08 Add first image + new directories
2024-02-17 Add datasheet for screen and Opamp
2024-05-20 Add RPi Pico Kicad library
2024-06-01 Add more pdfs
2024-06-01 Add a PSB imported from another project
2024-06-09 First version of PCB completed
2024-06-09 Add Gerber files sent to JLCPCB
2024-07-27 first version of micropython
2025-04-08 Add first version of software for both pico and PC
2025-04-08 Add progress bar to voltage display
2025-04-08 Fix color display
2025-04-08 Update history for sparkline
2025-04-09 Fix schematic errors - Regenerate a PCB for version 1.1
2026-03-05 Add hardware documentation and MicroPython conversion guide
    - Add connectors diagram (drawio)
    - Add schematic PDF
    - Add MicroPython conversion documentation
2026-03-05 Add MCP server and update PC application
    - Add MCP server with voltage monitoring tools
    - Refactor tools: get_voltages returns enabled channels with names
    - Add get_voltage (by name) and get_voltage_idx (by index)
    - Update get_channel_history to use channel names
2026-03-05 Add MicroPython firmware for Pico
    - Add boot.py and main.py for voltage reading
    - Add Makefile for deployment
2026-03-05 Add Python requirements
2026-06-10 Add KiCAD-MCP-Server mcp server setup
2026-06-11 Start new 2.0 version with 8 PWM-based DAC
2026-06-15 cleaning sche
2026-06-15 cleaned schematic, component placement on layout
2026-06-18 layout finished
2026-06-22 as sent for FAB
